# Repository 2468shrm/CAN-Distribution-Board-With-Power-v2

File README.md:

# CAN-Distribution-Board-With-Power-v2

## Board Layout

## Disclaimer
This board has not been fabricated or tested. It is to be considered
alpha and subject to bugs and errors. Use at your own risk. However the Gerbers
are provided should you want to fabricate your own.

## Enclosure

An 3D-printable enclosure is avaiable for this board. [Enclosure link](https://github.com/2468shrm/CAN-Distribution-Board-Enclosure).

## Introduction
This is a board created to simplify CAN wiring on FRC robots. It was created by the
mentors of FRC2468/2687/2689.

This board is a subset of the [CAN Distribution With Debug](https://github.com/2468shrm/CAN-Distribution-With-Debug) board.  The debug version of the board was created first and the
debug circuitry was removed while preserving the positions of the mounting holes and
connectors. This was done to share enclosures.

The board has 5 CAN connections and 3 power connections. The intended use is for
the CAN connections of either a swerve module or a WCD gearbox.
- Power
  - One connection upstream
  - One connection downstream
  - One connection to a local sensor (e.g. a CANcoder)
- CAN
  - One connection upstream
  - One connection downstream
  - One connection to a drive motor controller (Falcon 500, SPARK MAX)
  - One connection to a drive or steering motor
  - One connection to a CAN-connected sensor (CANcoder)

## CAN and Power Connections
The connectors for the CAN and power are WAGO 250-204s (X1, X2, X3, X4).

## Termination
The board contains a 2x2 header (J1) to allow for jumpers to be installed to enable
CAN termination.
- No jumpers means no termination
- One jumper provides 120 ohms termination (single end termination)
- Two jumpers provides 60 ohms termination (full termination)

Populating the termination circuitry is optional.

## Debug
THis board has two test point to probe CAN_H and CAN_L signal integrity.

# 3D Views of the Board
## Top

## Iso Front

## Iso Back

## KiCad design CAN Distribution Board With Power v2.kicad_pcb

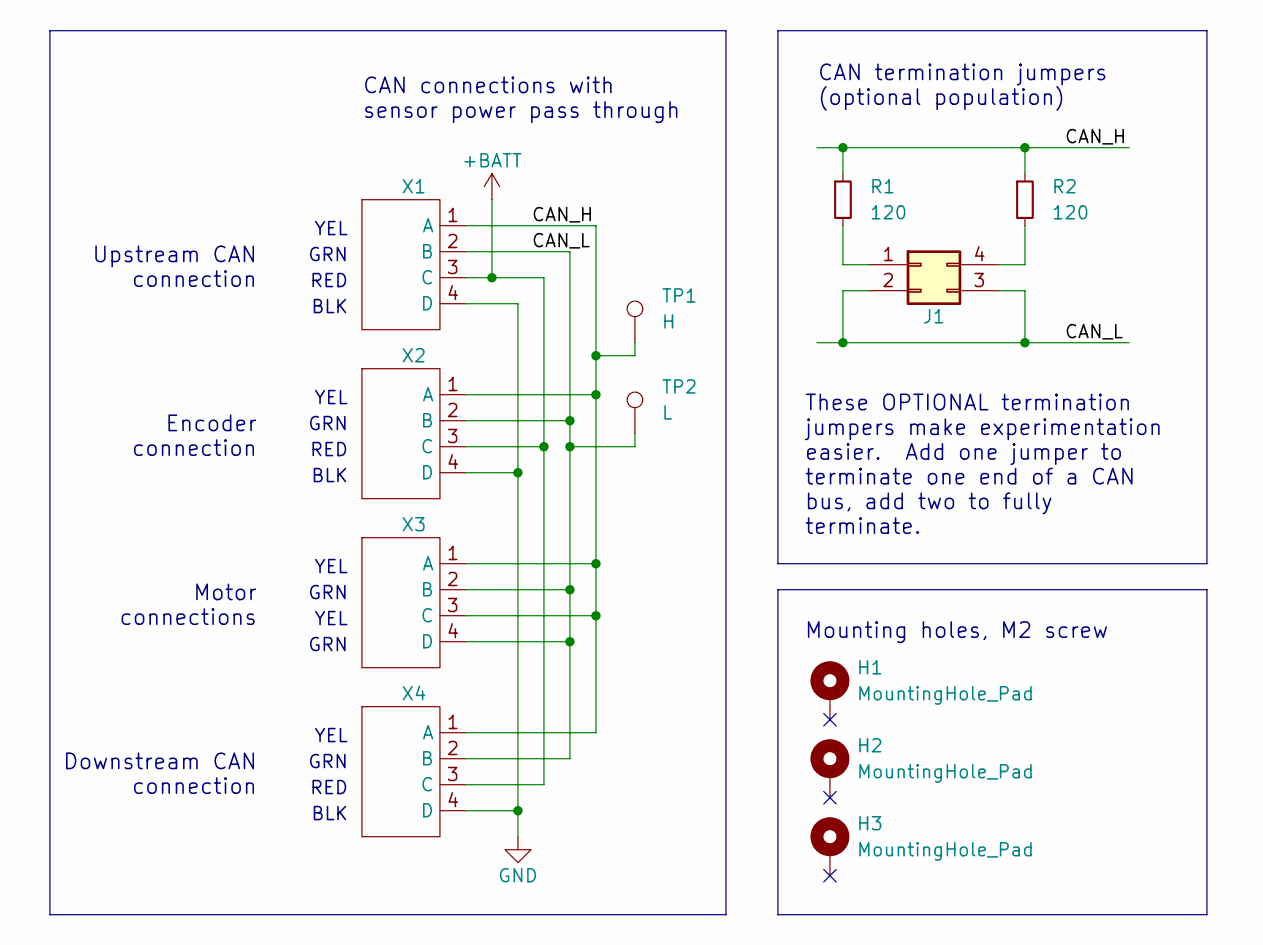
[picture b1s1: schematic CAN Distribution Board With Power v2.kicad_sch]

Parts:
H1, H2, H3: MountingHole_Pad; MountingHole_2.2mm_M2_Pad
J1: Conn_02x02_Counter_Clockwise; PinHeader_2x02_P2.54mm_Vertical
R1, R2: 120; R_0805_2012Metric
TP1: H; TestPoint_Pad_D1.5mm
TP2: L; TestPoint_Pad_D1.5mm
X1, X2, X3, X4: WAGO_250-204; WAGO 250-204

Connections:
+BATT: X1.3 (C), X2.3 (C), X4.3 (C)
/CAN_H: R1.1, R2.1, TP1.1, X1.1 (A), X2.1 (A), X3.1 (A), X3.3 (C), X4.1 (A)
/CAN_L: J1.2, J1.3, TP2.1, X1.2 (B), X2.2 (B), X3.2 (B), X3.4 (D), X4.2 (B)
GND: X1.4 (D), X2.4 (D), X4.4 (D)
unnamed: J1.1, R1.2
unnamed: J1.4, R2.2

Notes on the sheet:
BLK
GRN
YEL
CAN termination jumpers (optional population)
Encoder connection
RED
Upstream CAN connection
Mounting holes, M2 screw
These OPTIONAL termination jumpers make experimentation easier. Add one jumper to terminate one end of a CAN bus, add two to fully terminate.
CAN connections with sensor power pass through
Motor connections
Downstream CAN connection

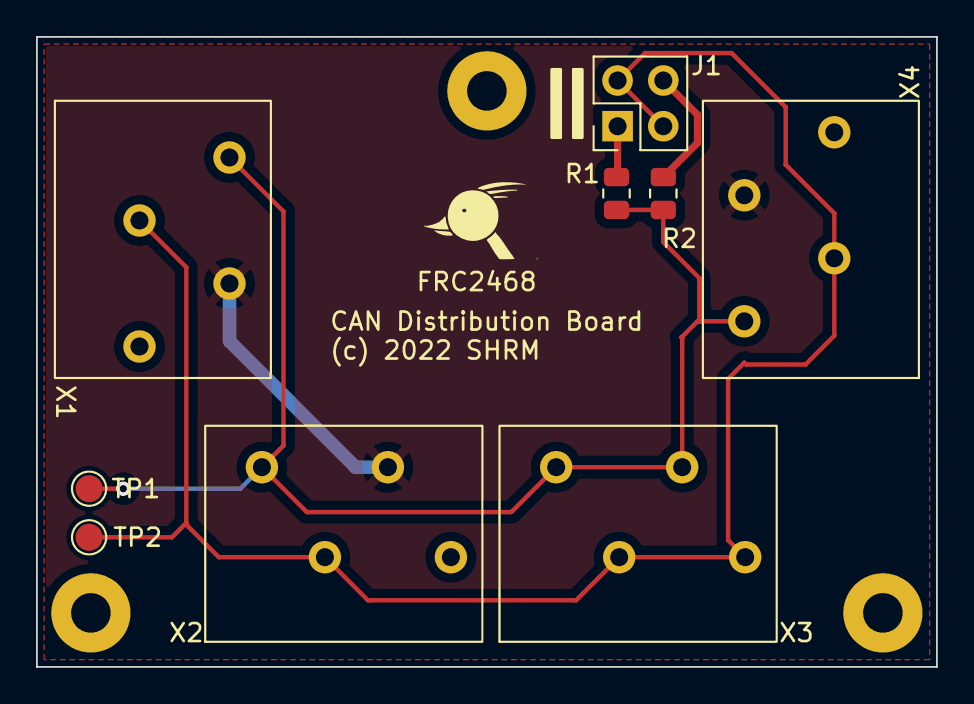
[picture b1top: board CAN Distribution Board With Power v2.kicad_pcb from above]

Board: 2 copper layers, 50.0 x 35.0 mm, 12 parts (0 on the bottom side), 6 nets.

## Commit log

2022-12-26 initial tech files
2023-01-06 added enclosure link to README
2023-01-06 added Gerber ZIP file.
2023-01-07 removing Gerbers.zip
2023-01-07 updated Gerbers.zip (added back)

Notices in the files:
CAN Distribution Board With Power v2.kicad_pcb:
(c) 2022 SHRM
